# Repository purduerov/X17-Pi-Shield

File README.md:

# X17-Pi-Shield
This board powers and connects sensors to the Pi

Whenever you make a new part, download the datasheet and save it here _**and**_ with the part in the parts library

Always pull other people's changes before beginning to work
`git pull`

Be sure to push your changes after  working on them. Run:
1. `git add .` to add any files in this directory or a subdirectory
or `git add -u` to add any modified files
2. (Optional) `git clean -nX` to see what ignored files can be removed
	`git clean -fX` removes ignored files (Eagle backups)
3. `git commit -m "helpful commit message"` with a description of the work that you did
4. `git push` to push your work to github

Other helpful commands
* `git status` says information about modified and staged files
* `git log` shows the recent commits of the repository
* `git log filename.extension` show the recent commits for just that file
* `git checkout first-couple-letter-of-commit-id` lets you go back to a previous version
* `git checkout master` brings you back to the latest commit
* `git tag` lists the tags
* `git tag -a orderX -m "the version of the board placed for the X'th order"` tag a specific commit
* `git push --tags` needed to push tags to remote
* `git show orderX` show the commit log for the given tag
* `git checkout orderX` go back and interact with the files at the tagged commit

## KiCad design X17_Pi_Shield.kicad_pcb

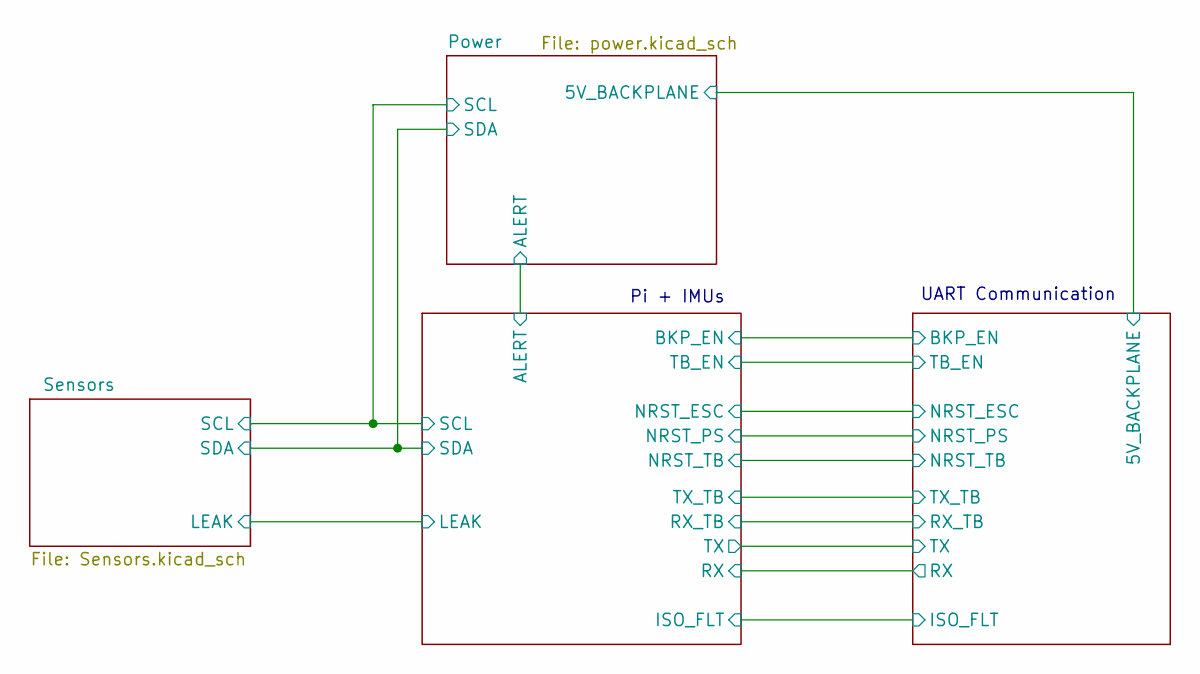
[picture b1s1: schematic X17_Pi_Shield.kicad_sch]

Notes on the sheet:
UART Communication
Pi + IMUs

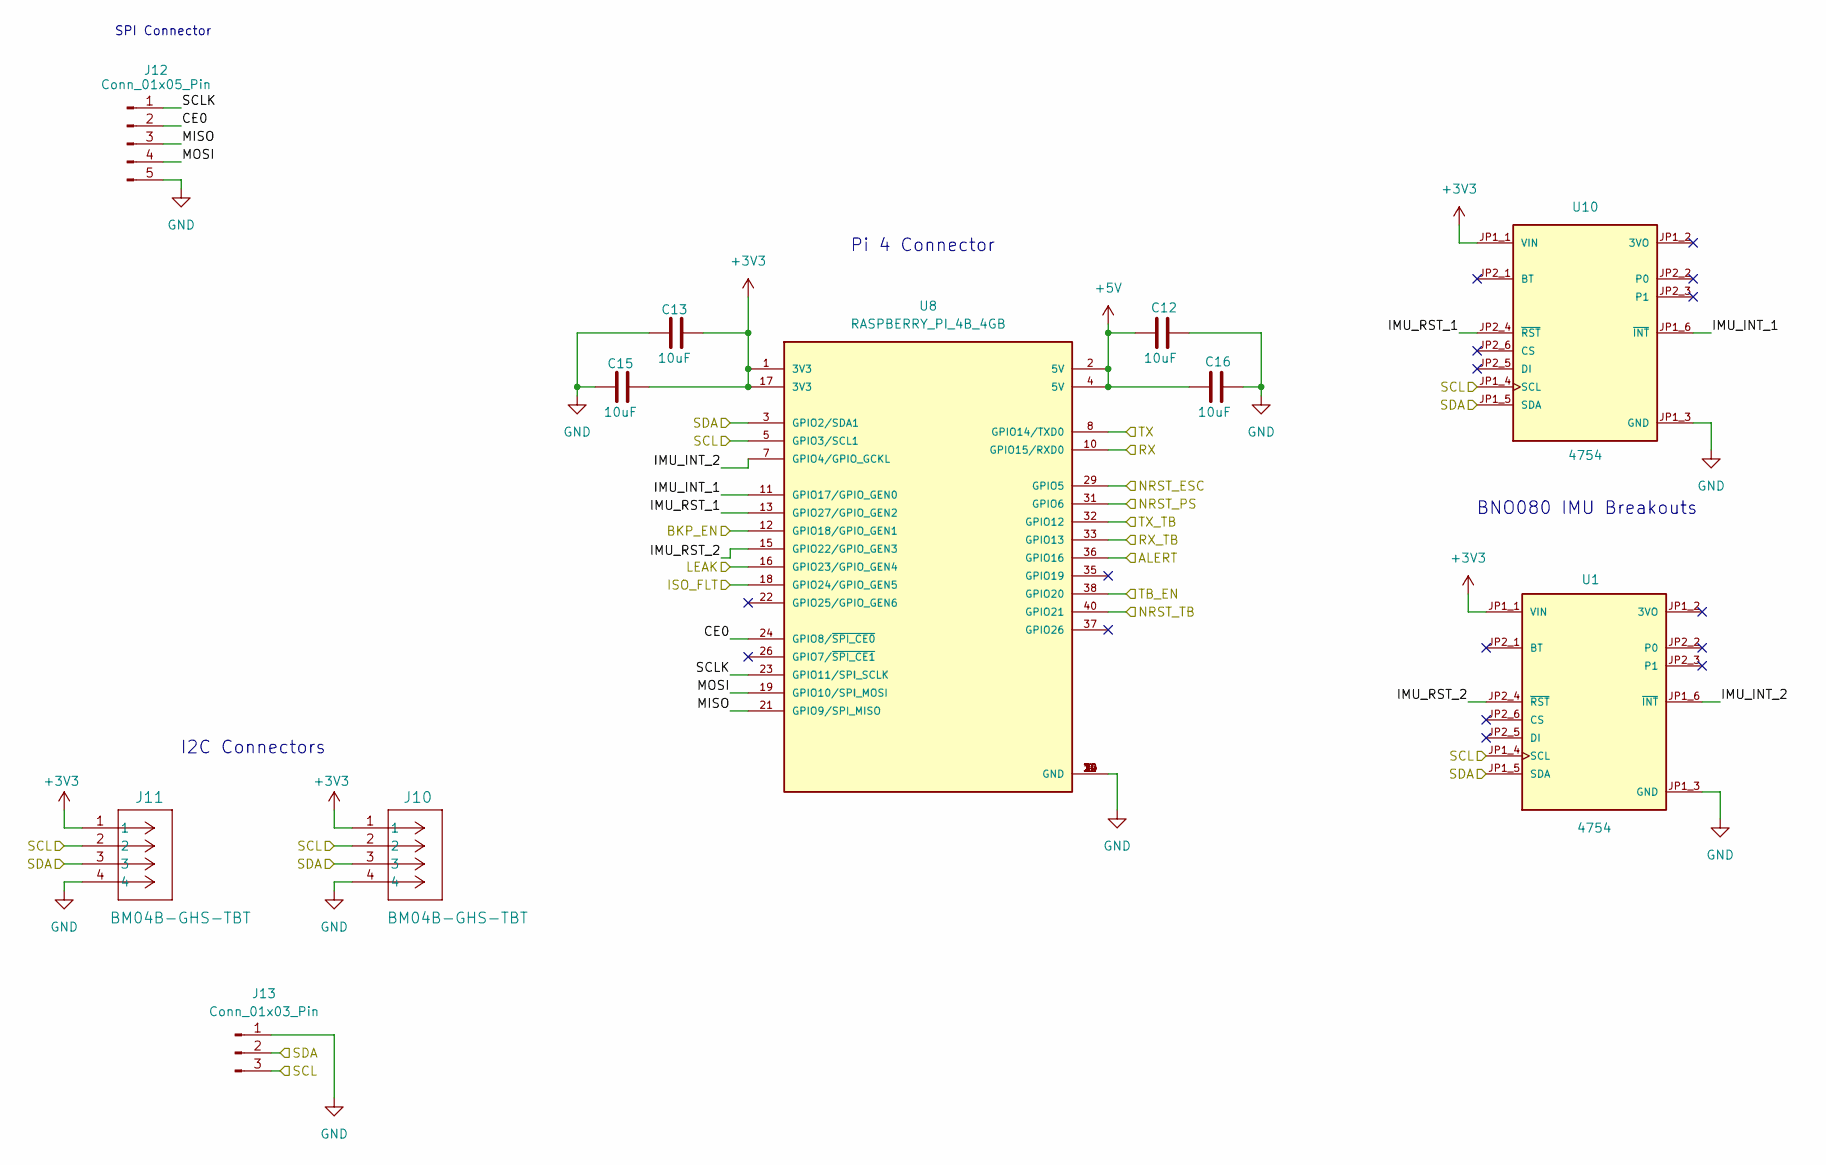
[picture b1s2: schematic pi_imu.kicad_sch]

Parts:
C12, C13, C15, C16: 10uF; C_0603_1608Metric_Pad1.08x0.95mm_HandSolder
J10, J11: BM04B-GHS-TBT; JST_GH_BM04B-GHS-TBT_1x04-1MP_P1.25mm_Vertical
J12: Conn_01x05_Pin; PinHeader_1x05_P2.54mm_Vertical
J13: Conn_01x03_Pin; PinHeader_1x03_P2.54mm_Vertical
U1, U10: 4754; MODULE_4754; PARTREV 2021-03-16
U8: RASPBERRY_PI_4B_4GB; SAMTEC_TSW-120-09-G-D; PARTREV 4

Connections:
+3V3: C13.1, C15.1, J10.1, J11.1, U1.JP1_1 (VIN), U8.1 (3V3), U8.17 (3V3), U10.JP1_1 (VIN); also elsewhere on the board
+5V: C12.2, C16.2, U8.2 (5V), U8.4 (5V); also elsewhere on the board
/Pi + IMU/ALERT: U8.36 (GPIO16); also elsewhere on the board
/Pi + IMU/BKP_EN: U8.12 (GPIO18/GPIO_GEN1); also elsewhere on the board
/Pi + IMU/CE0: J12.2, U8.24 (GPIO8/~SPI_CE0)
/Pi + IMU/IMU_INT_1: U8.11 (GPIO17/GPIO_GEN0), U10.JP1_6 (~INT)
/Pi + IMU/IMU_INT_2: U1.JP1_6 (~INT), U8.7 (GPIO4/GPIO_GCKL)
/Pi + IMU/IMU_RST_1: U8.13 (GPIO27/GPIO_GEN2), U10.JP2_4 (~RST)
/Pi + IMU/IMU_RST_2: U1.JP2_4 (~RST), U8.15 (GPIO22/GPIO_GEN3)
/Pi + IMU/ISO_FLT: U8.18 (GPIO24/GPIO_GEN5); also elsewhere on the board
/Pi + IMU/LEAK: U8.16 (GPIO23/GPIO_GEN4); also elsewhere on the board
/Pi + IMU/MISO: J12.3, U8.21 (GPIO9/SPI_MISO)
/Pi + IMU/MOSI: J12.4, U8.19 (GPIO10/SPI_MOSI)
/Pi + IMU/NRST_ESC: U8.29 (GPIO5); also elsewhere on the board
/Pi + IMU/NRST_PS: U8.31 (GPIO6); also elsewhere on the board
/Pi + IMU/NRST_TB: U8.40 (GPIO21); also elsewhere on the board
/Pi + IMU/RX: U8.10 (GPIO15/RXD0); also elsewhere on the board
/Pi + IMU/RX_TB: U8.33 (GPIO13); also elsewhere on the board
/Pi + IMU/SCL: J10.2, J11.2, J13.3, U1.JP1_4 (SCL), U8.5 (GPIO3/SCL1), U10.JP1_4 (SCL); also elsewhere on the board
/Pi + IMU/SCLK: J12.1, U8.23 (GPIO11/SPI_SCLK)
/Pi + IMU/SDA: J10.3, J11.3, J13.2, U1.JP1_5 (SDA), U8.3 (GPIO2/SDA1), U10.JP1_5 (SDA); also elsewhere on the board
/Pi + IMU/TB_EN: U8.38 (GPIO20); also elsewhere on the board
/Pi + IMU/TX: U8.8 (GPIO14/TXD0); also elsewhere on the board
/Pi + IMU/TX_TB: U8.32 (GPIO12); also elsewhere on the board
GND: C12.1, C13.2, C15.2, C16.1, J10.4, J11.4, J12.5, J13.1, U1.JP1_3 (GND), U8.6 (GND), U8.9 (GND), U8.14 (GND), U8.20 (GND), U8.25 (GND), U8.30 (GND), U8.34 (GND), U8.39 (GND), U10.JP1_3 (GND); also elsewhere on the board
unnamed 43: U1.JP2_5 (DI); also elsewhere on the board

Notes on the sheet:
BNO080 IMU Breakouts
I2C Connectors
SPI Connector
Pi 4 Connector

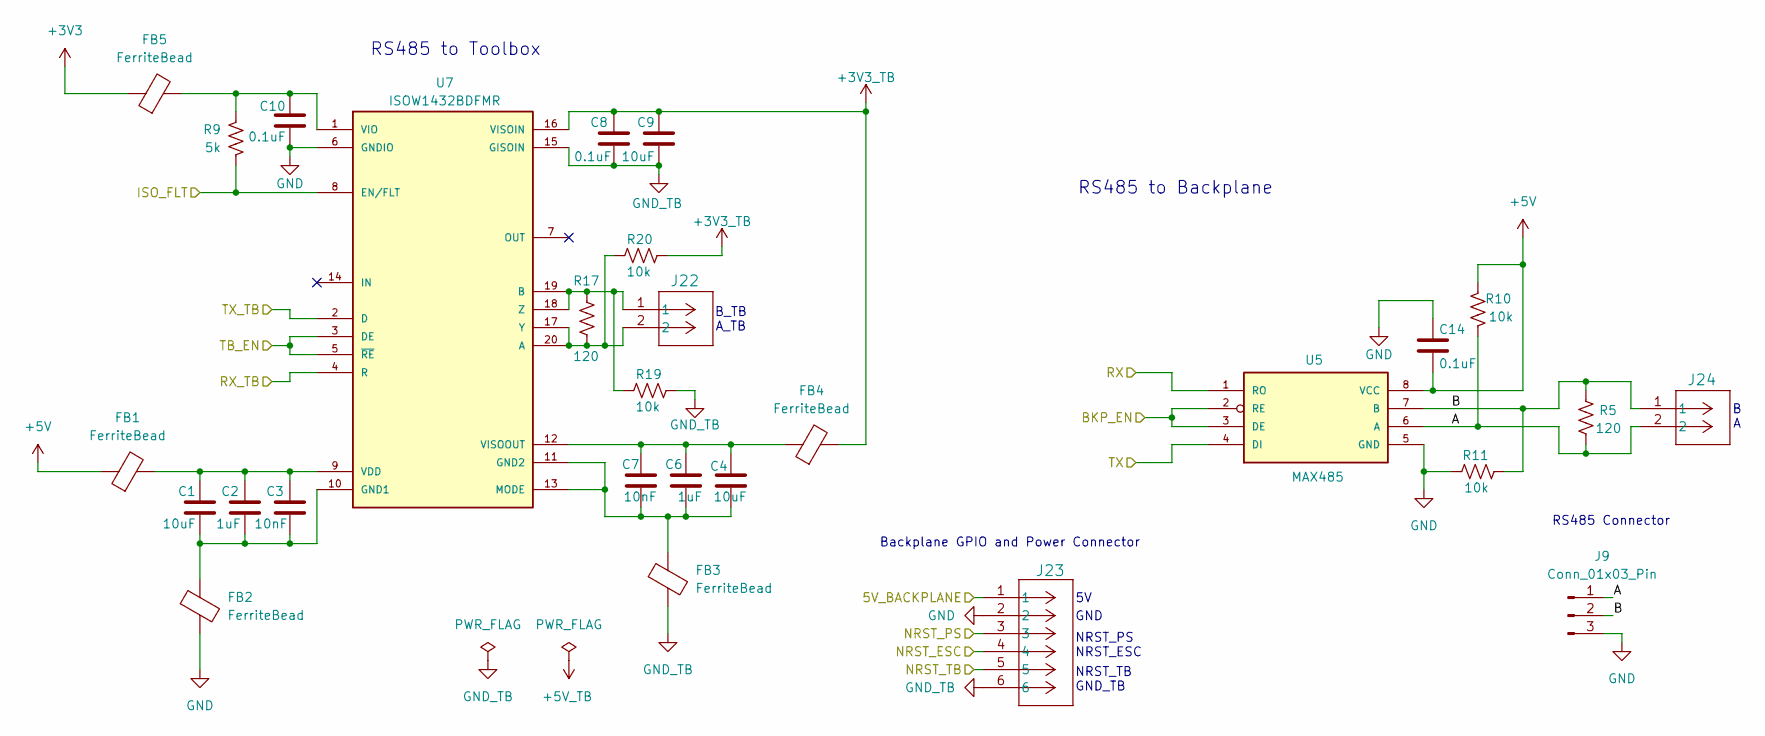
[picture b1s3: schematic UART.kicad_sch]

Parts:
C1, C4, C9: 10uF; C_0603_1608Metric_Pad1.08x0.95mm_HandSolder
C2, C6: 1uF; C_0603_1608Metric_Pad1.08x0.95mm_HandSolder
C3, C7: 10nF; C_0603_1608Metric_Pad1.08x0.95mm_HandSolder
C8, C10, C14: 0.1uF; C_0603_1608Metric_Pad1.08x0.95mm_HandSolder
FB1, FB2, FB3, FB4, FB5: FerriteBead; C_0603_1608Metric_Pad1.08x0.95mm_HandSolder
J9: Conn_01x03_Pin; PinHeader_1x03_P2.54mm_Vertical
J22, J24: 430450212; CON_430450212_MOL
J23: 430450612; CON_430450612_MOL
R5, R17: 120; R_0603_1608Metric_Pad0.98x0.95mm_HandSolder
R9: 5k; R_0603_1608Metric_Pad0.98x0.95mm_HandSolder
R10, R11, R19, R20: 10k; R_0603_1608Metric_Pad0.98x0.95mm_HandSolder
U5: MAX485; SO08
U7: ISOW1432BDFMR; SOIC127P1030X355-20N; PARTREV B

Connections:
+3V3: FB5.1; also elsewhere on the board
+3V3_TB: C8.1, C9.1, FB4.2, R20.2, U7.16 (VISOIN)
+5V: C14.2, FB1.1, R10.1, U5.8 (VCC); also elsewhere on the board
/Pi + IMU/BKP_EN: U5.2 (RE), U5.3 (DE); also elsewhere on the board
/Pi + IMU/ISO_FLT: R9.1, U7.8 (EN/FLT); also elsewhere on the board
/Pi + IMU/NRST_ESC: J23.4; also elsewhere on the board
/Pi + IMU/NRST_PS: J23.3; also elsewhere on the board
/Pi + IMU/NRST_TB: J23.5; also elsewhere on the board
/Pi + IMU/RX: U5.1 (RO); also elsewhere on the board
/Pi + IMU/RX_TB: U7.4 (R); also elsewhere on the board
/Pi + IMU/TB_EN: U7.3 (DE), U7.5 (~RE); also elsewhere on the board
/Pi + IMU/TX: U5.4 (DI); also elsewhere on the board
/Pi + IMU/TX_TB: U7.2 (D); also elsewhere on the board
/Power/5V_BACKPLANE: J23.1; also elsewhere on the board
/UART/A: J9.1, J24.2, R5.2, R10.2, U5.6 (A)
/UART/B: J9.2, J24.1, R5.1, R11.1, U5.7 (B)
GND: C10.1, C14.1, FB2.2, J9.3, J23.2, R11.2, U5.5 (GND), U7.6 (GNDIO); also elsewhere on the board
GND_TB: C8.2, C9.2, FB3.2, J23.6, R19.2, U7.15 (GISOIN)
unnamed: J22.2, R17.2, R20.1, U7.17 (Y), U7.20 (A)
unnamed: J22.1, R17.1, R19.1, U7.18 (Z), U7.19 (B)
unnamed: C1.2, C2.2, C3.2, FB2.1, U7.10 (GND1)
unnamed: C4.2, C6.2, C7.2, FB3.1, U7.11 (GND2), U7.13 (MODE)
unnamed: C1.1, C2.1, C3.1, FB1.2, U7.9 (VDD)
unnamed: C10.2, FB5.2, R9.2, U7.1 (VIO)
unnamed: C4.1, C6.1, C7.1, FB4.1, U7.12 (VISOOUT)

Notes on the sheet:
GND
RS485 to Backplane
B_TB A_TB
RS485 Connector
NRST_TB GND_TB
RS485 to Toolbox
B A
NRST_PS NRST_ESC
Backplane GPIO and Power Connector

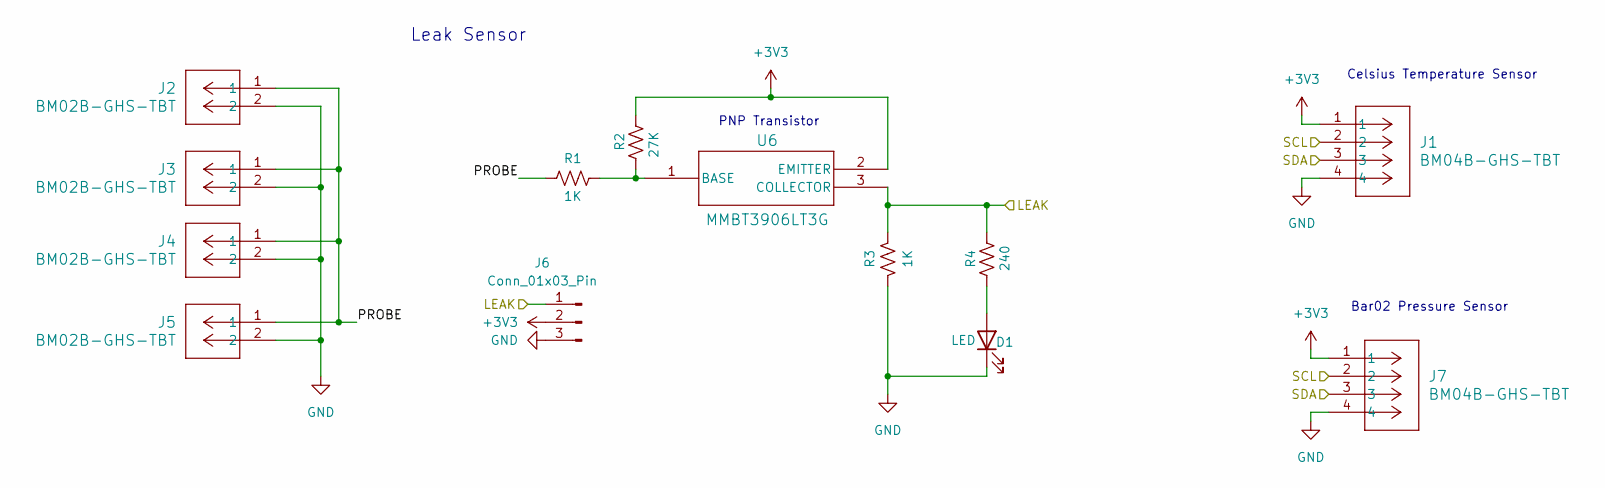
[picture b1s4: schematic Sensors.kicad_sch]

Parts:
D1: LED; LED_0805_2012Metric_Pad1.15x1.40mm_HandSolder
J1, J7: BM04B-GHS-TBT; JST_GH_BM04B-GHS-TBT_1x04-1MP_P1.25mm_Vertical
J2, J3, J4, J5: BM02B-GHS-TBT; CONN_BM02B-GHS-TBT_JST
J6: Conn_01x03_Pin; PinHeader_1x03_P2.54mm_Vertical
R1, R3: 1K; R_0603_1608Metric_Pad0.98x0.95mm_HandSolder
R2: 27K; R_0603_1608Metric_Pad0.98x0.95mm_HandSolder
R4: 240; R_0603_1608Metric_Pad0.98x0.95mm_HandSolder
U6: MMBT3906LT3G; SOT-23-3_1P4X3P040_ONS

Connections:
+3V3: J1.1, J6.2, J7.1, R2.2, U6.2 (EMITTER); also elsewhere on the board
/Pi + IMU/LEAK: J6.1, R3.2, R4.1, U6.3 (COLLECTOR); also elsewhere on the board
/Pi + IMU/SCL: J1.2, J7.2; also elsewhere on the board
/Pi + IMU/SDA: J1.3, J7.3; also elsewhere on the board
/Sensors/PROBE: J2.1, J3.1, J4.1, J5.1, R1.1
GND: D1.1 (K), J1.4, J2.2, J3.2, J4.2, J5.2, J6.3, J7.4, R3.1; also elsewhere on the board
unnamed: D1.2 (A), R4.2
unnamed: R1.2, R2.1, U6.1 (BASE)

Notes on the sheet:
Leak Sensor
PNP Transistor
Bar02 Pressure Sensor
Celsius Temperature Sensor

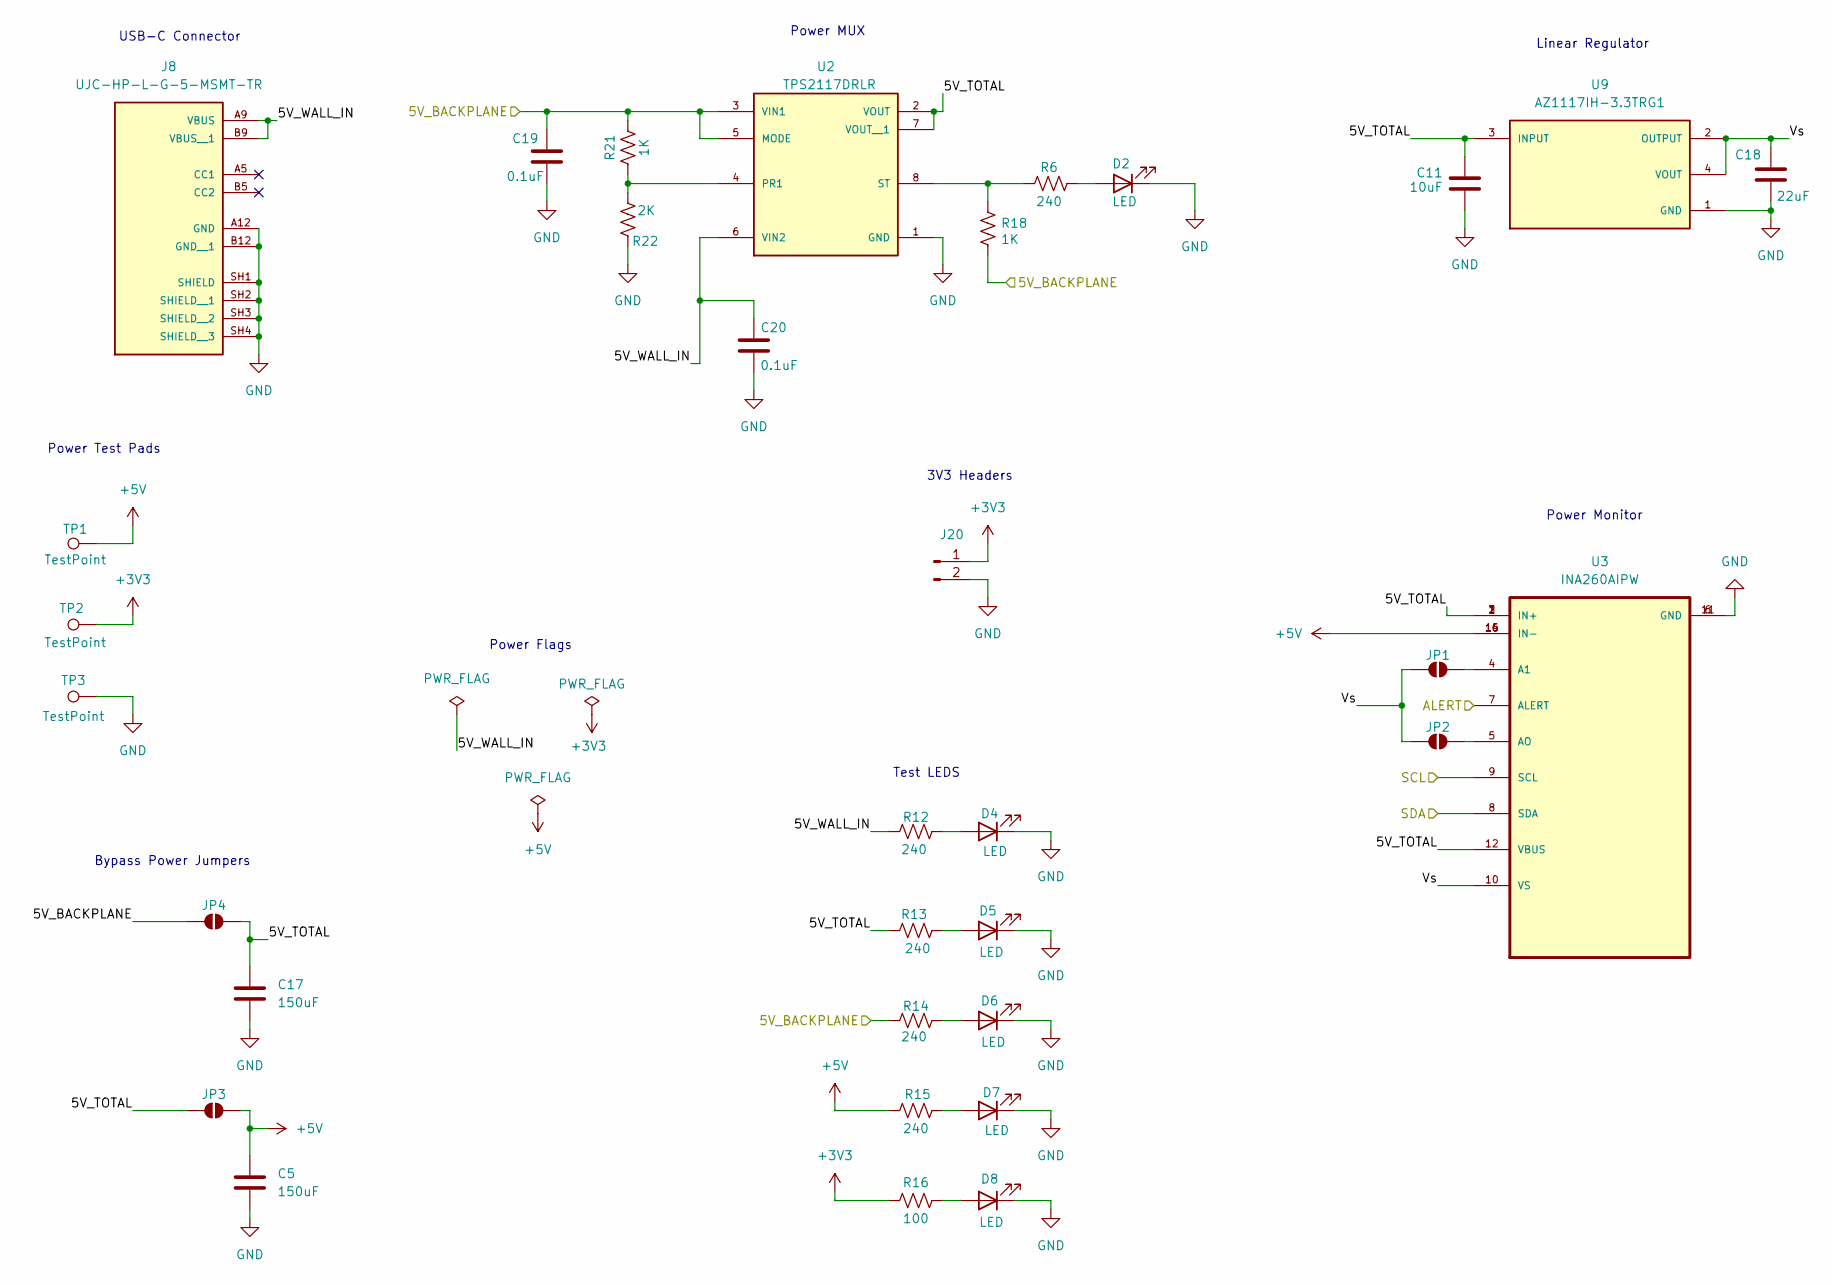
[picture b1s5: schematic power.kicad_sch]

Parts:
C5, C17: 150uF; C_1210_3225Metric_Pad1.33x2.70mm_HandSolder
C11: 10uF; C_0603_1608Metric_Pad1.08x0.95mm_HandSolder
C18: 22uF; C_0603_1608Metric_Pad1.08x0.95mm_HandSolder
C19, C20: 0.1uF; C_0603_1608Metric_Pad1.08x0.95mm_HandSolder
D2, D4, D5, D6, D7, D8: LED; LED_0805_2012Metric_Pad1.15x1.40mm_HandSolder
J8: UJC-HP-L-G-5-MSMT-TR; CUI_UJC-HP-L-G-5-MSMT-TR; PARTREV 1.01
J20: Conn_01x02_Pin; PinHeader_1x02_P2.54mm_Vertical
JP1, JP2, JP3, JP4: SolderJumper_2_Open; SolderJumper-2_P1.3mm_Open_RoundedPad1.0x1.5mm
R6, R12, R13, R14, R15: 240; R_0603_1608Metric_Pad0.98x0.95mm_HandSolder
R16: 100; R_0603_1608Metric_Pad0.98x0.95mm_HandSolder
R18, R21: 1K; R_0603_1608Metric_Pad0.98x0.95mm_HandSolder
R22: 2K; R_0603_1608Metric_Pad0.98x0.95mm_HandSolder
TP1, TP2, TP3: TestPoint; TestPoint_Pad_D4.0mm
U2: TPS2117DRLR; SOTFL50P160X60-8N; PARTREV A
U3: INA260AIPW; SOP65P640X120-16N
U9: AZ1117IH-3.3TRG1; SOT230P700X185-4N; PARTREV 2-2

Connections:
+3V3: J20.1, R16.1, TP2.1; also elsewhere on the board
+5V: C5.1, JP3.2 (B), R15.1, TP1.1, U3.14 (IN-), U3.15 (IN-), U3.16 (IN-); also elsewhere on the board
/Pi + IMU/ALERT: U3.7 (ALERT); also elsewhere on the board
/Pi + IMU/SCL: U3.9 (SCL); also elsewhere on the board
/Pi + IMU/SDA: U3.8 (SDA); also elsewhere on the board
/Power/5V_BACKPLANE: C19.2, JP4.1 (A), R14.1, R18.2, R21.1, U2.3 (VIN1), U2.5 (MODE); also elsewhere on the board
/Power/5V_TOTAL: C11.1, C17.1, JP3.1 (A), JP4.2 (B), R13.1, U2.2 (VOUT), U2.7 (VOUT__1), U3.1 (IN+), U3.2 (IN+), U3.3 (IN+), U3.12 (VBUS), U9.3 (INPUT)
/Power/5V_WALL_IN: C20.1, J8.A9 (VBUS), J8.B9 (VBUS__1), R12.1, U2.6 (VIN2)
/Power/Vs: C18.1, JP1.1 (A), JP2.1 (A), U3.10 (VS), U9.2 (OUTPUT), U9.4 (VOUT)
GND: C5.2, C11.2, C17.2, C18.2, C19.1, C20.2, D2.1 (K), D4.1 (K), D5.1 (K), D6.1 (K), D7.1 (K), D8.1 (K), J8.A12 (GND), J8.B12 (GND__1), J8.SH1 (SHIELD), J8.SH2 (SHIELD__1), J8.SH3 (SHIELD__2), J8.SH4 (SHIELD__3), J20.2, R22.2, TP3.1, U2.1 (GND), U3.6 (GND), U3.11 (GND), U9.1 (GND); also elsewhere on the board
unnamed: D2.2 (A), R6.2
unnamed: D4.2 (A), R12.2
unnamed: D5.2 (A), R13.2
unnamed: D6.2 (A), R14.2
unnamed: D7.2 (A), R15.2
unnamed: D8.2 (A), R16.2
unnamed: JP1.2 (B), U3.4 (A1)
unnamed: JP2.2 (B), U3.5 (AO)
unnamed: R21.2, R22.1, U2.4 (PR1)
unnamed: R6.1, R18.1, U2.8 (ST)

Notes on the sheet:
Power MUX
Power Monitor
Power Flags
3V3 Headers
Power Test Pads
USB-C Connector
Linear Regulator
Test LEDS
Bypass Power Jumpers

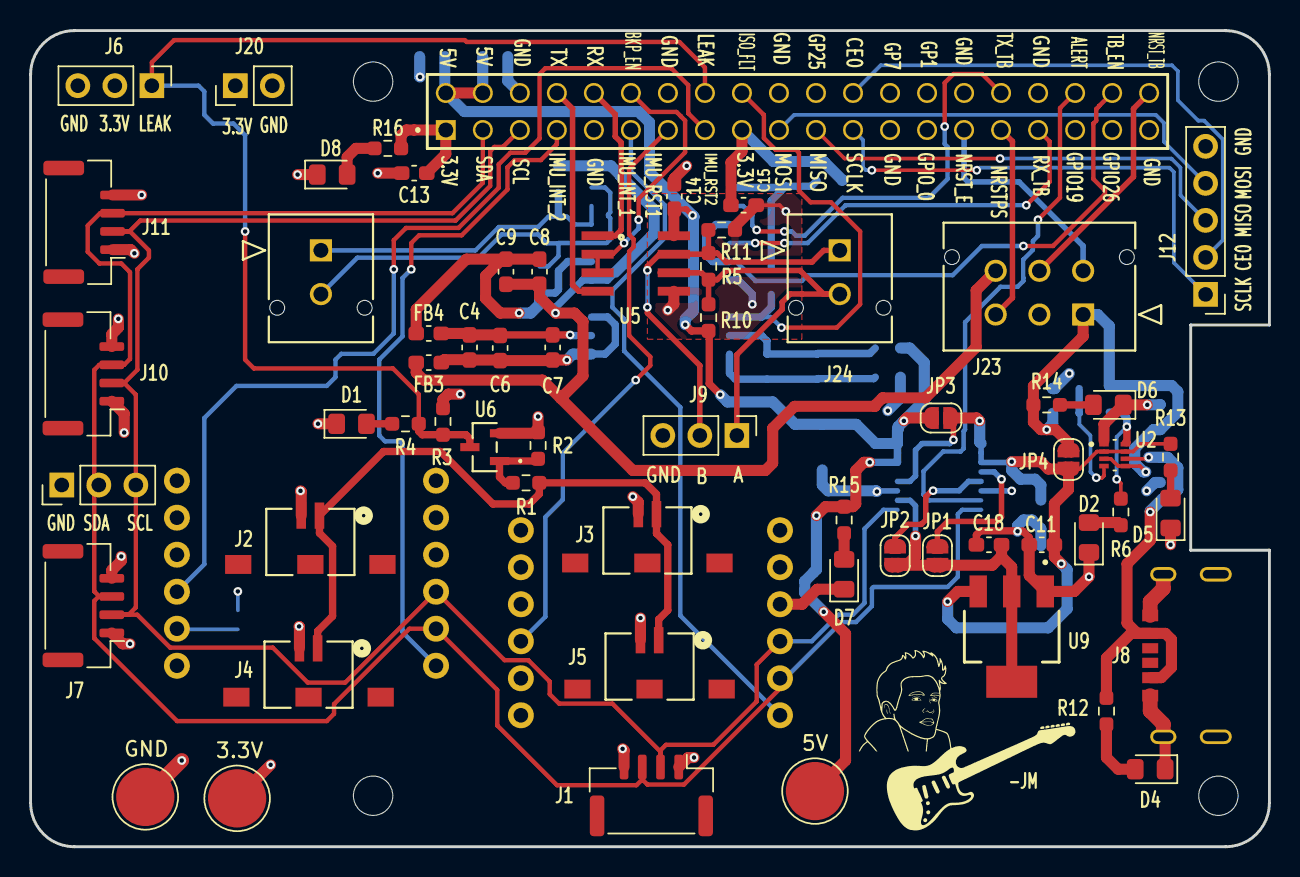
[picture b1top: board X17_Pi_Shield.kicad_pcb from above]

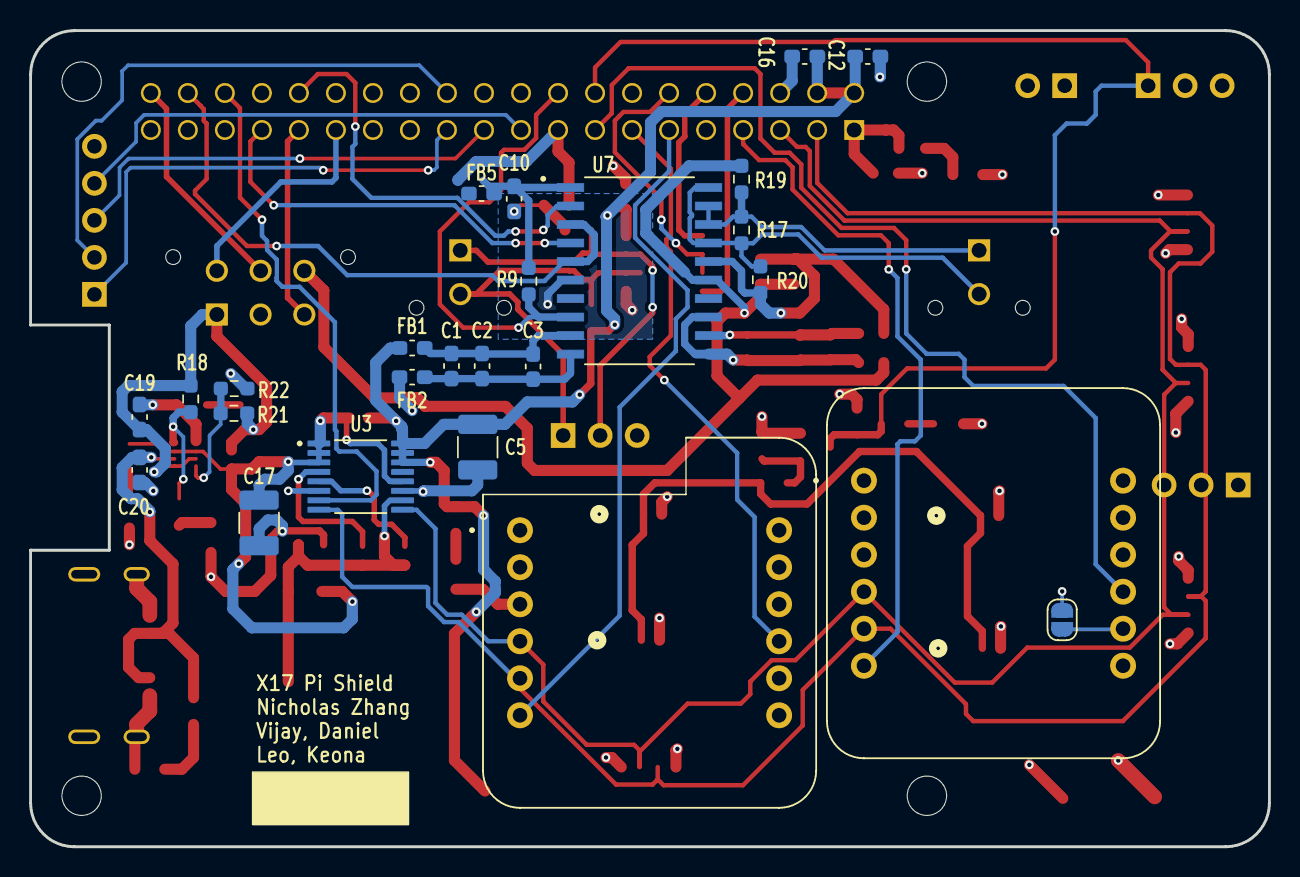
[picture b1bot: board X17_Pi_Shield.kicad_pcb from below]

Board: 4 copper layers, 85.0 x 56.0 mm, 86 parts (25 on the bottom side), 54 nets.

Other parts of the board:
JP5: SolderJumper_2_Open; SolderJumper-2_P1.3mm_Open_RoundedPad1.0x1.5mm

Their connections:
+3V3: JP5.1 (A); also elsewhere on the board
unnamed 43: JP5.2 (B); also elsewhere on the board

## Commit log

2024-09-25 Initial Commit: Adding KiCad files
2024-10-09 Schematic and Library Update
2024-10-12 Hierarchy Schematic Update
2024-10-19 Added New Libraries and Schematic Updates
2024-10-22 Root Update and Adding ISO Pt1
2024-10-22 Adding Libraries
2024-10-22 board dimensions
2024-10-23 Finalizing Schematic
2024-10-24 Final Schematic Update
2024-10-24 Updated Hiearchal Root Sheet
2024-10-26 Sensor Connector Update
2024-10-26 Library Update
2024-11-02 Pre-Toolbox Final
2024-11-02 re-add dimensions
2024-11-07 Finalized Footprints
2024-11-07 Updating 3d Models
2024-11-09 Added header and updated mounting pins
2024-11-13 Initial Component Placement
2024-11-14 Init Pos Workday
2024-11-18 Routing
2024-11-19 Updated Silkscreen
2024-11-21 Layout
2024-11-22 Bruh
2024-11-22 Unconnected Fix
2024-11-23 Pre Design Review - Reviewed DRC Errors
2024-12-05 Pre 4 Layer Routing
2024-12-15 Hello Bruh
2024-12-15 Routing Additions
2024-12-16 Finished Routing
2024-12-17 Finished Layout + Updated Capacitor Sizes for 150uF
2024-12-17 Tweaking 150uF
2024-12-18 Silkscreen
2024-12-18 Fixed MAX485 Schematic
2024-12-18 MAX 485
2024-12-20 Last Updates + Adding Screenshots
2024-12-30 fixed several DRC errors and ferrite bead package size, still reviewing the board
2025-01-08 completed my review of pi-shield. doublechecked schematics referenced to datasheets, added solder jump to set IMU address, adjusted solder mask
2025-01-10 all files added
2025-02-15 Fixed Silkscreen orientation/ USB-C 3d Model
